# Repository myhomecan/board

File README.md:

# board

Schematic and PCB source files

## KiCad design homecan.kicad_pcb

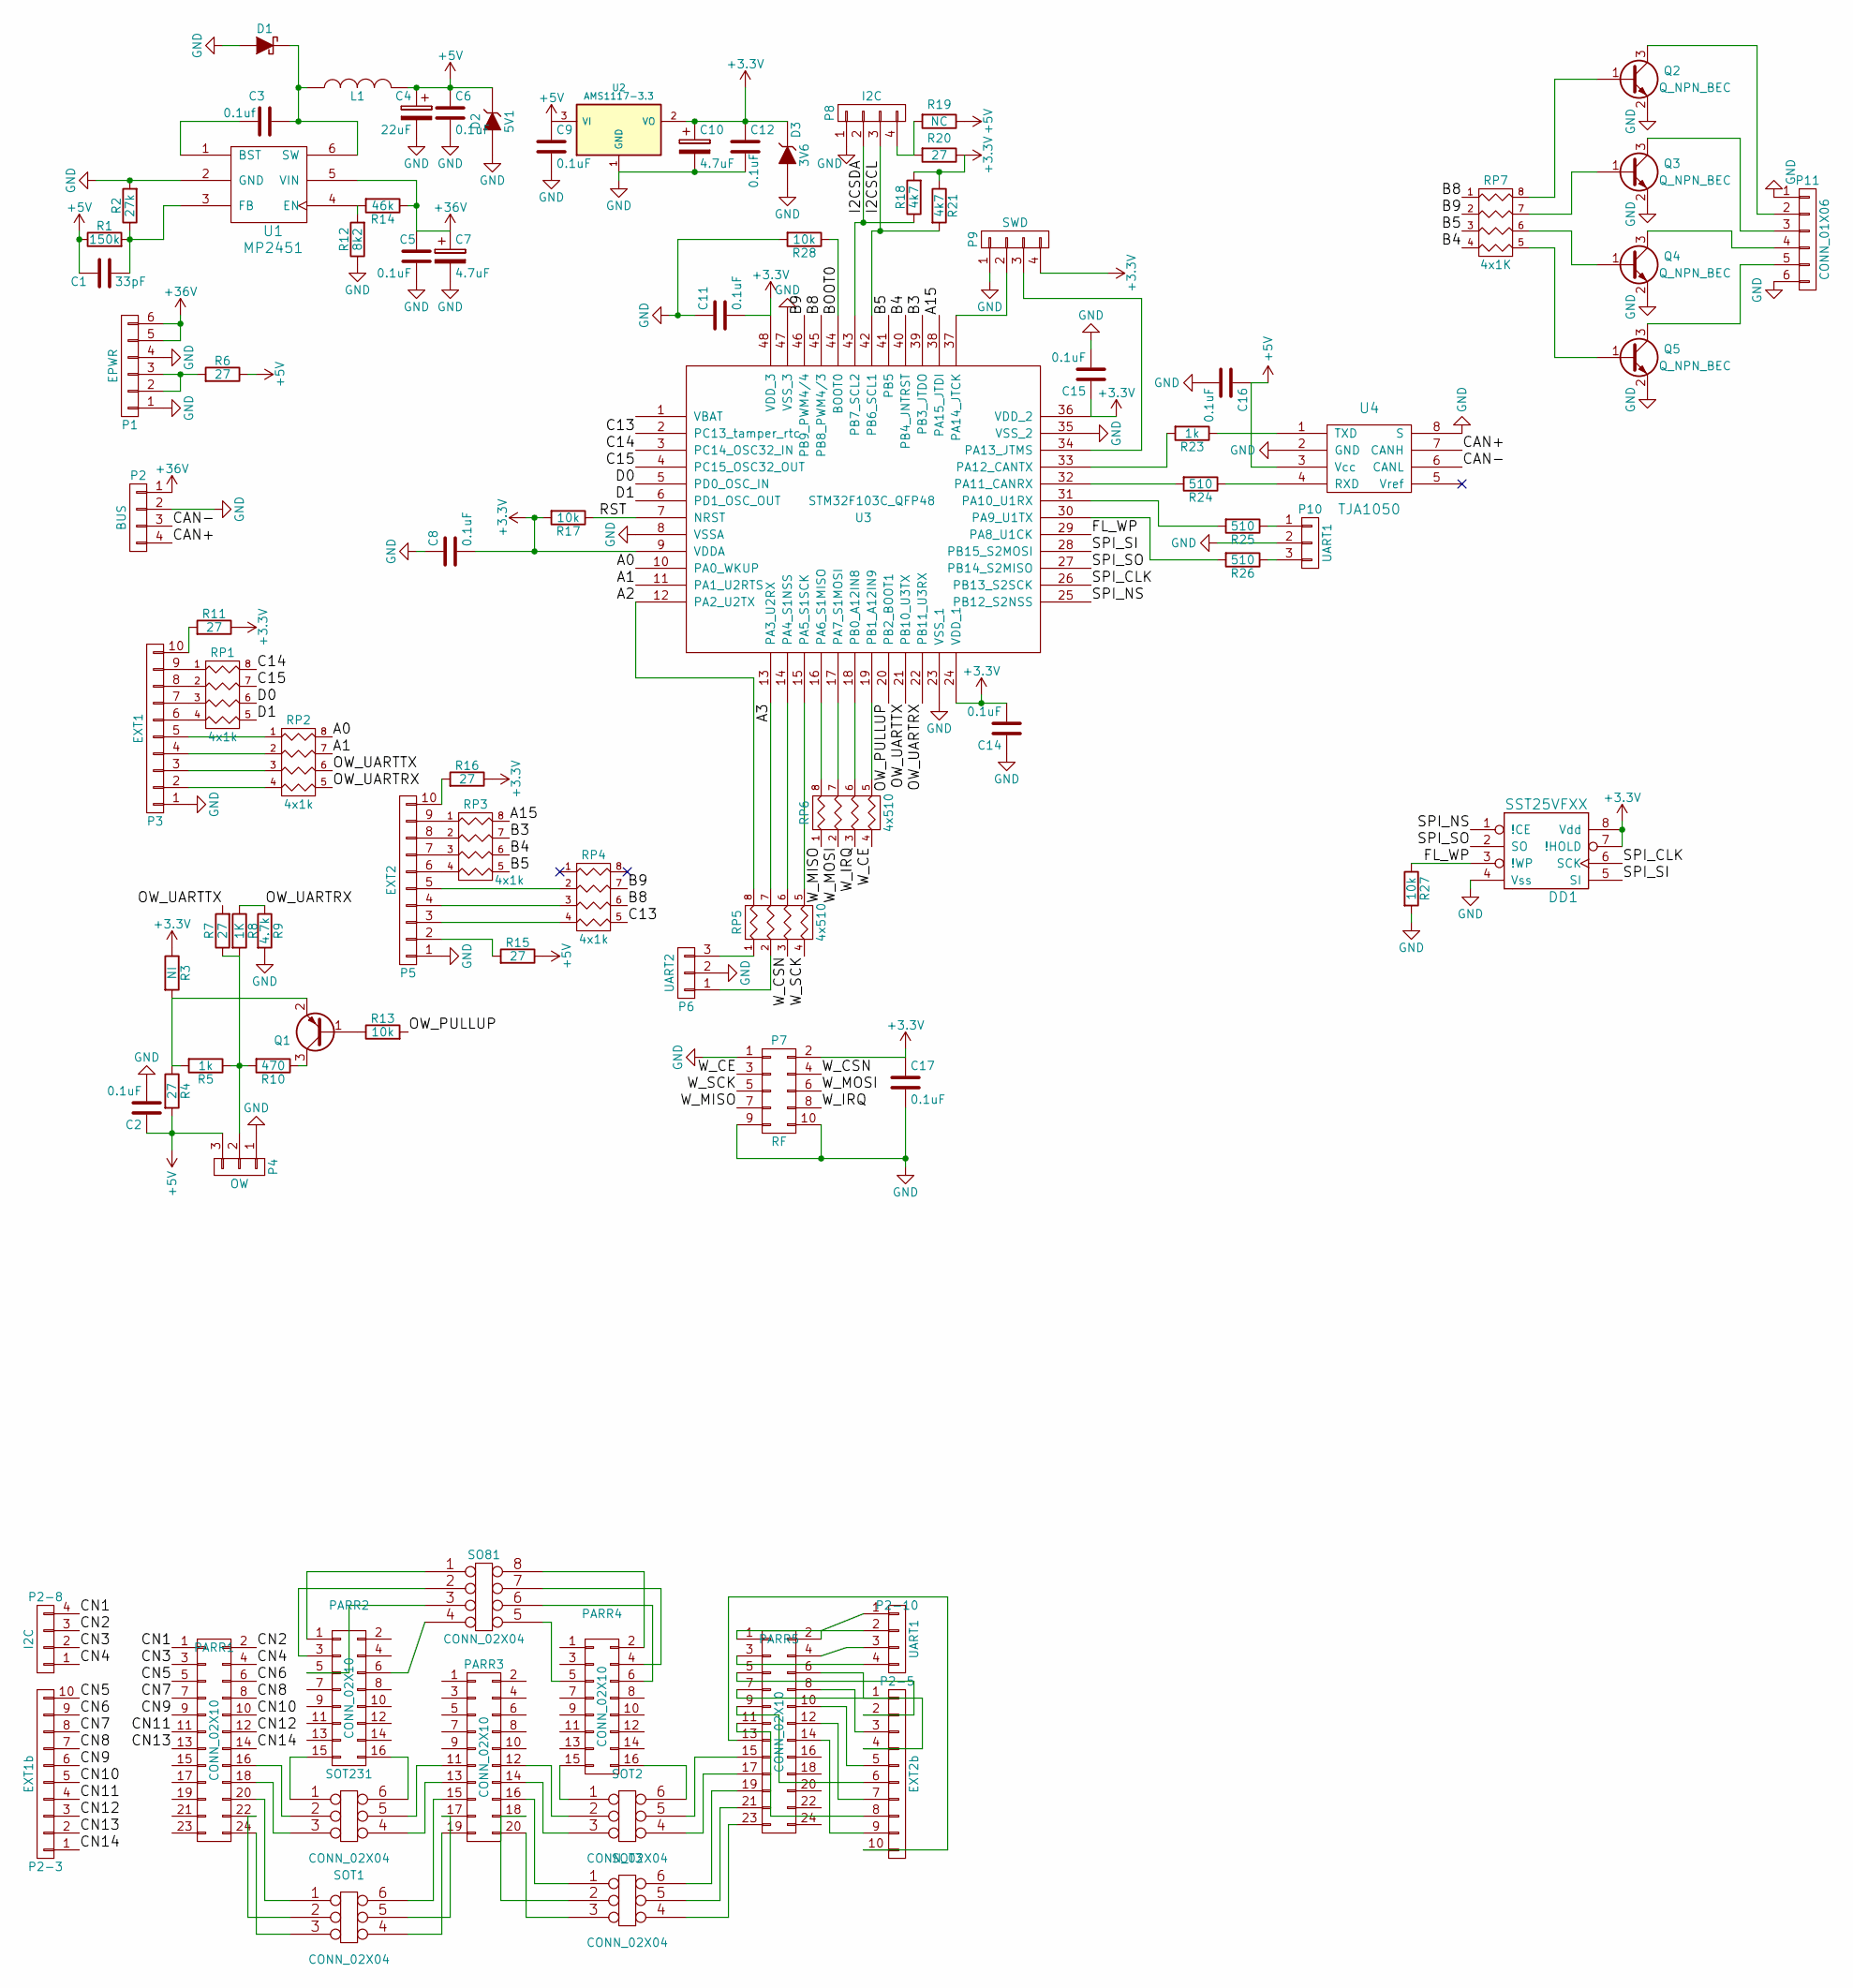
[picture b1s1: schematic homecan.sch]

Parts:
C1: 33pF; C_0805
C2, C5, C6, C8, C9, C11, C12, C14, C15, C16, C17: 0.1uF; C_0805
C3: 0.1uf; C_0805
C4: 22uF; TantalC_SizeC_EIA-6032_Reflow
C7, C10: 4.7uF; C_1206
D1: D_Schottky; SOD-123
D2: 5V1; SOD-123
D3: 3V6; SOD-123
DD1: SST25VFXX; SOIC-8_3.9x4.9mm_Pitch1.27mm
L1: Ihlp2525czer6r8m01 6.8UH; Choke_SMD_6.3x6.3_H3
P1: EPWR; Pin_Header_Straight_1x06
P2: BUS; bornier4
P2-3: EXT1b; Pin_Header_Straight_1x10_Pitch1.27mm
P2-5: EXT2b; Pin_Header_Straight_1x10_Pitch1.27mm
P2-8, P8: I2C; Pin_Header_Straight_1x4_Pitch1.27mm
P2-10, P10: UART1; Pin_Header_Straight_1x4_Pitch1.27mm
P3: EXT1; Pin_Header_Straight_1x10_Pitch1.27mm
P4: OW; bornier3
P5: EXT2; Pin_Header_Straight_1x10_Pitch1.27mm
P6: UART2; Pin_Header_Straight_1x03
P7: RF; Pin_Header_Straight_2x05
P9: SWD; Pin_Header_Straight_1x4_Pitch1.27mm
P11: CONN_01X06; Pin_Header_Straight_1x06
PARR1, PARR5: CONN_02X10; Pin_Header_Straight_2x12
PARR2, PARR4: CONN_02X10; Pin_Header_Straight_2x08
PARR3: CONN_02X10; Pin_Header_Straight_2x10
Q1: Q_PNP_BEC; SOT-23
Q2, Q3, Q4, Q5: Q_NPN_BEC; SOT-23
R1: 150k; R_0805
R2: 27k; R_0805
R3: NI; R_0805
R4, R6, R7, R11, R15, R16, R20: 27; R_0805
R5, R23: 1k; R_0805
R8: 1K; R_0805
R9: 4.7k; R_0805
R10: 470; R_0805
R12: 8k2; R_0805
R13, R27: 10k; R_0805
R14: 46k; R_0805
R17, R28: 10k; R_0402
R18, R21: 4k7; R_0805
R19: NC; R_0805
R24, R25, R26: 510; R_0805
RP1, RP2, RP3, RP4: 4x1k; R_Array_Convex_4x0402
RP5, RP6: 4x510; R_Array_Convex_4x0402
RP7: 4x1K; R_Array_Convex_4x0402
SO81: CONN_02X04; SOIC-8-N
SOT1, SOT2, SOT3, SOT231: CONN_02X04; SOT-23-6
U1: MP2451; SOT-23-6
U2: AMS1117-3.3; SOT-223
U3: STM32F103C_QFP48; LQFP-48_7x7mm_Pitch0.5mm
U4: TJA1050; SOIC-8_3.9x4.9mm_Pitch1.27mm

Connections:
+3V3: C8.2, C10.1, C11.2, C12.1, C14.2, C15.1, C17.1, D3.2 (K), DD1.7 (!HOLD), DD1.8 (Vdd), P7.2, P9.4, R3.1, R11.1, R16.1, R17.2, R18.2, R20.1, R21.1, U2.2 (VO), U3.9 (VDDA), U3.24 (VDD_1), U3.36 (VDD_2), U3.48 (VDD_3)
+5V: C1.1, C2.1, C4.1, C6.1, C9.1, C16.1, D2.2 (K), L1.2, P4.3, R1.1, R4.2, R6.1, R15.1, R19.1, U2.3 (VI), U4.3 (Vcc)
+36V: C5.1, C7.1, P1.5, P1.6, P2.1, R14.1, U1.5 (VIN)
/A0: RP2.8 (R1), U3.10 (PA0_WKUP)
/A1: RP2.7 (R2), U3.11 (PA1_U2RTS)
/A2: RP5.8 (R1), U3.12 (PA2_U2TX)
/A3: RP5.7 (R2), U3.13 (PA3_U2RX)
/A15: RP3.8 (R1), U3.38 (PA15_JTDI)
/B3: RP3.7 (R2), U3.39 (PB3_JTDO)
/B4: RP3.6 (R3), RP7.4, U3.40 (PB4_JNTRST)
/B5: RP3.5 (R4), RP7.3, U3.41 (PB5)
/B8: RP4.6 (R3), RP7.1, U3.45 (PB8_PWM4/3)
/B9: RP4.7 (R2), RP7.2, U3.46 (PB9_PWM4/4)
/BOOT0: R28.1, U3.44 (BOOT0)
/C13: RP4.5 (R4), U3.2 (PC13_tamper_rtc)
/C14: RP1.8 (R1), U3.3 (PC14_OSC32_IN)
/C15: RP1.7 (R2), U3.4 (PC15_OSC32_OUT)
/CAN+: P2.4, U4.7 (CANH)
/CAN-: P2.3, U4.6 (CANL)
/CN1: P2-8.4, PARR1.1
/CN2: P2-8.3, PARR1.2
/CN3: P2-8.2, PARR1.3
/CN4: P2-8.1, PARR1.4
/CN5: P2-3.10, PARR1.5
/CN6: P2-3.9, PARR1.6
/CN7: P2-3.8, PARR1.7
/CN8: P2-3.7, PARR1.8
/CN9: P2-3.6, PARR1.9
/CN10: P2-3.5, PARR1.10
/CN11: P2-3.4, PARR1.11
/CN12: P2-3.3, PARR1.12
/CN13: P2-3.2, PARR1.13
/CN14: P2-3.1, PARR1.14
/D0: RP1.6 (R3), U3.5 (PD0_OSC_IN)
/D1: RP1.5 (R4), U3.6 (PD1_OSC_OUT)
/FL_WP: DD1.3 (!WP), R27.1, U3.29 (PA8_U1CK)
/I2CSCL: P8.3, R21.2, U3.42 (PB6_SCL1)
/I2CSDA: P8.2, R18.1, U3.43 (PB7_SCL2)
/OW_PULLUP: R13.2, U3.20 (PB2_BOOT1)
/OW_UARTRX: R8.1, R9.1, RP2.5 (R4), U3.22 (PB11_U3RX)
/OW_UARTTX: R7.2, RP2.6 (R3), U3.21 (PB10_U3TX)
/RST: R17.1, U3.7 (NRST)
/SPI_CLK: DD1.6 (SCK), U3.26 (PB13_S2SCK)
/SPI_NS: DD1.1 (!CE), U3.25 (PB12_S2NSS)
/SPI_SI: DD1.5 (SI), U3.28 (PB15_S2MOSI)
/SPI_SO: DD1.2 (SO), U3.27 (PB14_S2MISO)
/W_CE: P7.3, RP6.4
/W_CSN: P7.4, RP5.3
/W_IRQ: P7.8, RP6.3
/W_MISO: P7.7, RP6.1
/W_MOSI: P7.6, RP6.2
/W_SCK: P7.5, RP5.4
GND: C2.2, C4.2, C5.2, C6.2, C7.2, C8.1, C9.2, C10.2, C11.1, C12.2, C14.1, C15.2, C16.2, C17.2, D1.1 (A), D2.1 (A), D3.1 (A), DD1.4 (Vss), P1.1, P1.4, P2.2, P3.1, P4.1, P5.1, P6.2, P7.1, P7.9, P7.10, P8.1, P9.1, P10.2, P11.1, P11.6, Q2.2 (E), Q3.2 (E), Q4.2 (E), Q5.2 (E), R2.2, R9.2, R12.1, R27.2, R28.2, U1.2 (GND), U2.1 (GND), U3.8 (VSSA), U3.23 (VSS_1), U3.35 (VSS_2), U3.47 (VSS_3), U4.2 (GND), U4.8 (S)
unnamed: C1.2, R1.2, R2.1, U1.3 (FB)
unnamed: C3.1, D1.2 (K), L1.1, U1.6 (SW)
unnamed: C3.2, U1.1 (BST)
unnamed: P1.2, P1.3, R6.2
unnamed: P2-5.1, PARR5.6
unnamed: P2-5.2, PARR5.5
unnamed: P2-5.3, PARR5.8
unnamed: P2-5.4, PARR5.7
unnamed: P2-5.5, PARR5.10
unnamed: P2-5.6, PARR5.9
unnamed: P2-5.7, PARR5.12
unnamed: P2-5.8, PARR5.11
unnamed: P2-5.9, PARR5.14
unnamed: P2-5.10, PARR5.13
unnamed: P2-10.1, PARR5.2
unnamed: P2-10.2, PARR5.1
unnamed: P2-10.3, PARR5.4
unnamed: P2-10.4, PARR5.3
unnamed: P3.2, RP2.4
unnamed: P3.3, RP2.3
unnamed: P3.4, RP2.2
unnamed: P3.5, RP2.1
unnamed: P3.6, RP1.4
unnamed: P3.7, RP1.3
unnamed: P3.8, RP1.2
unnamed: P3.9, RP1.1
unnamed: P3.10, R11.2
unnamed: P4.2, R5.1, R7.1, R8.2, R10.2
unnamed: P5.2, R15.2
unnamed: P5.3, RP4.4
unnamed: P5.4, RP4.3
unnamed: P5.5, RP4.2
unnamed: P5.6, RP3.4
unnamed: P5.7, RP3.3
unnamed: P5.8, RP3.2
unnamed: P5.9, RP3.1
unnamed: P5.10, R16.2
unnamed: P6.1, RP5.2
unnamed: P6.3, RP5.1
unnamed: P8.4, R19.2, R20.2
unnamed: P9.2, U3.37 (PA14_JTCK)
unnamed: P9.3, U3.34 (PA13_JTMS)
unnamed: P10.1, R25.1
unnamed: P10.3, R26.1
unnamed: P11.2, Q2.3 (C)
unnamed: P11.3, Q3.3 (C)
unnamed: P11.4, Q4.3 (C)
unnamed: P11.5, Q5.3 (C)
unnamed: PARR1.16, SOT231.2
unnamed: PARR1.18, SOT231.3
unnamed: PARR1.20, SOT1.1
unnamed: PARR1.22, SOT1.2
unnamed: PARR1.24, SOT1.3
unnamed: PARR2.1, SO81.1
unnamed: PARR2.3, SO81.2
unnamed: PARR2.5, SO81.3
unnamed: PARR2.6, SO81.4
unnamed: PARR2.15, SOT231.1
unnamed: PARR2.16, SOT231.6
unnamed: PARR3.11, SOT231.5
unnamed: PARR3.12, SOT2.2
unnamed: PARR3.13, SOT231.4
unnamed: PARR3.14, SOT2.3
unnamed: PARR3.15, SOT1.6
unnamed: PARR3.16, SOT3.1
unnamed: PARR3.17, SOT1.5
unnamed: PARR3.18, SOT3.2
unnamed: PARR3.19, SOT1.4
unnamed: PARR3.20, SOT3.3
unnamed: PARR4.2, SO81.8
unnamed: PARR4.4, SO81.7
unnamed: PARR4.5, SO81.5
unnamed: PARR4.6, SO81.6
unnamed: PARR4.15, SOT2.1
unnamed: PARR4.16, SOT2.6
unnamed: PARR5.15, SOT2.5
unnamed: PARR5.17, SOT2.4
unnamed: PARR5.19, SOT3.6
unnamed: PARR5.21, SOT3.5
unnamed: PARR5.23, SOT3.4
unnamed: Q1.1 (B), R13.1
unnamed: Q1.2 (E), R3.2, R4.1, R5.2
unnamed: Q1.3 (C), R10.1
unnamed: Q2.1 (B), RP7.8 (R1)
unnamed: Q3.1 (B), RP7.7 (R2)
unnamed: Q4.1 (B), RP7.6 (R3)
unnamed: Q5.1 (B), RP7.5 (R4)
unnamed: R12.2, R14.2, U1.4 (EN)
unnamed: R23.1, U4.1 (TXD)
unnamed: R23.2, U3.33 (PA12_CANTX)
unnamed: R24.1, U4.4 (RXD)
unnamed: R24.2, U3.32 (PA11_CANRX)
unnamed: R25.2, U3.31 (PA10_U1RX)
unnamed: R26.2, U3.30 (PA9_U1TX)
unnamed: RP5.5 (R4), U3.15 (PA5_S1SCK)
unnamed: RP5.6 (R3), U3.14 (PA4_S1NSS)
unnamed: RP6.5 (R4), U3.19 (PB1_A12IN9)
unnamed: RP6.6 (R3), U3.18 (PB0_A12IN8)
unnamed: RP6.7 (R2), U3.17 (PA7_S1MOSI)
unnamed: RP6.8 (R1), U3.16 (PA6_S1MISO)

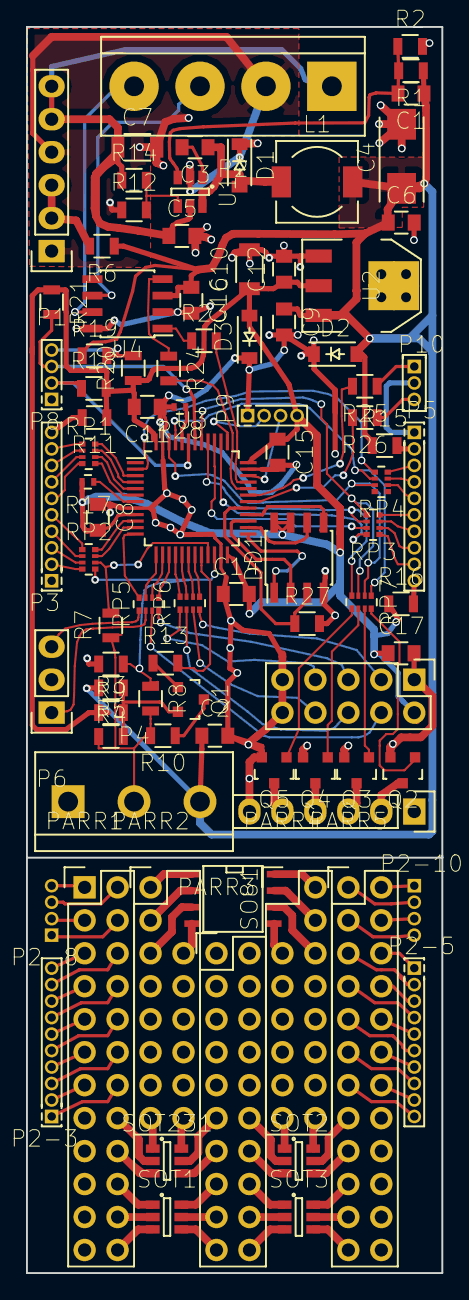
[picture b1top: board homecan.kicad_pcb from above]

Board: 2 copper layers, 32.0 x 96.0 mm, 89 parts (0 on the bottom side), 153 nets.
